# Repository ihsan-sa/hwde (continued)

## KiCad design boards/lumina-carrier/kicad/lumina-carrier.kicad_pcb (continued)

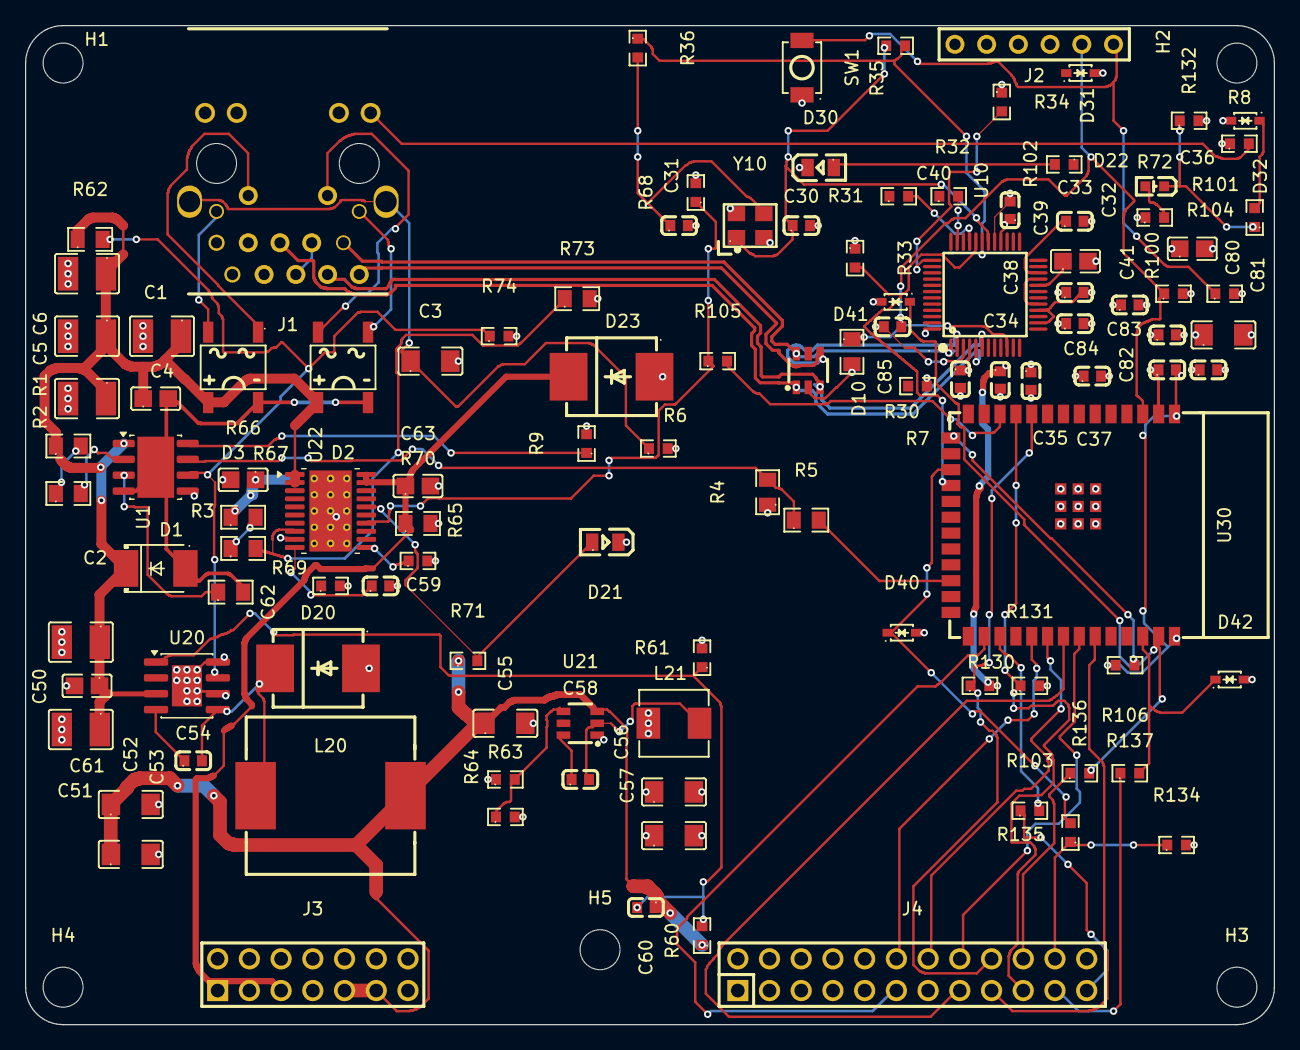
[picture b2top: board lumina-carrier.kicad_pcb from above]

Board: 4 copper layers, 100.0 x 80.0 mm, 116 parts (0 on the bottom side), 85 nets.

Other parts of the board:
H1, H2, H3, H4: MountingHole_3.2mm_M3

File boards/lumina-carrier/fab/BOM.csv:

Comment,Designator,Footprint,LCSC
100nF 100V X7R 0805,"C1,C61,C62,C63",C0805,C28233
10uF 100V X7R 1210,"C2,C4,C5,C6",C1210,C5156756
1nF 2kV X7R 1206,C3,C1206,C9196
27pF 50V NP0 0603,"C30,C31",C0603,C107045
4.7uF 25V X5R 0805,"C32,C36",C0805,C1779
10nF 50V X7R 0603,"C33,C59",C0603,C57112
100nF 50V X7R 0603,"C34,C35,C37,C38,C39,C40,C41,C54,C58",C0603,C14663
2.2uF 100V X7R 1210,"C50,C51",C1210,C153036
22uF 25V X5R 1206,"C52,C53,C55,C56,C57",C1206,C380359
150pF 50V NP0 0603,C60,C0603,C107038
22uF 25V X5R,C80,C1206,C380359
100nF 50V X7R,"C81,C82,C83",C0603,C14663
1uF 50V X5R,"C84,C85",C0603,C15849
SMBJ58A 58V 600W TVS,D1,SMB_L4.3-W3.6-LS5.4-R-RD,C2891331
ABS210 2A 1000V bridge (Alt A),D2,ABF_L5.1-W4.4-P4.00-LS6.2-BL,C2892567
ABS210 2A 1000V bridge (Alt B),D3,ABF_L5.1-W4.4-P4.00-LS6.2-BL,C2892567
TPD4E1U06 4ch 0.55pF ESD array,D10,SOT-23-6_L2.9-W1.6-P0.95-LS2.8-BR,C19829453
SS510C 100V 5A Schottky SMC,"D20,D23",SMC_L7.1-W6.2-LS8.1-R-RD,C19229
Green LED 0805,"D21,D30",LED0805-R-RD,C2297
Red LED 0603,D22,LED-SMD_L1.6-W0.8-R-RD,C2286
PESD3V3L1BA 3.3V ESD clamp SOD-323,"D31,D32,D40,D41,D42",SOD-323_L1.7-W1.3-LS2.6-BI,C2687129
LPJG0926HENL PoE+ RJ45 magjack,J1,RJ45-TH_LPJG0926HENL_C22457393,C22457393
1x6 2.54mm header (recovery),J2,CONN-TH_DS1021-1X6SF11-B,C7430362
DS1021-2x7SF11-B 2x7 male header,J3,HDR-TH_14P-P2.54-V-M-R2-C7-S2.54-1,C7430403
DS1021-2x12SF11-B 2x12 male header,J4,HDR-TH_24P-P2.54-V-M-R2-C12-S2.54,C7430408
68uH 3A 140mohm inductor,L20,IND-SMD_L12.6-W13.5,C526032
4.7uH 4A 46mohm inductor,L21,IND-SMD_L5.4-W5.2,C325964
12.1k 1% 0805,"R1,R2",R0805,C17431
90.9R 1% 0805,R3,R0805,C3000584
10k 1% 0805,"R4,R5",R0805,C17414
1M 1% 0603,"R6,R35",R0603,C22935
330R 1% 0603,"R7,R8,R72",R0603,C23138
0R jumper 0603,"R9,R36",R0603,C21189
12.4k 1% 0805,R30,R0805,C30908
22R 1% 0603,"R31,R32",R0603,C23345
10k 1% 0603,"R33,R34,R64,R69,R71,R106,R132,R134",R0603,C25804
270k 1% 0603,R60,R0603,C22965
30k 1% 0603,"R61,R68",R0603,C22984
100k 1% 0805,"R62,R70",R0805,C149504
33k 1% 0603,R63,R0603,C4216
18k 1% 0603,R65,R0603,C25810
620k 0.1% 0805,R66,R0805,C865592
10k 0.1% 0805,R67,R0805,C110775
12k 0.1% 0805,R73,R0805,C865172
4.7k 1% 0603,"R74,R130,R131",R0603,C23162
10k,"R100,R101",R0603,C25804
330R,R102,R0603,C23138
1k 1% 0603,"R103,R104,R105,R135,R136,R137",R0603,C21190
SMD tactile switch,SW1,SW-SMD_L3.9-W3.0-P4.45,C720477
TPS2378DDAR,U1,SOIC-8-1EP_3.9x4.9mm_P1.27mm_EP2.95x4.9mm_Mask2.71x3.4mm,C337500
W5500,U10,LQFP-48_L7.0-W7.0-P0.50-LS9.0-BL,C32843
SCT2A25STER,U20,SOIC-8-1EP_3.9x4.9mm_P1.27mm_EP2.41x3.3mm,C5124114
TPS563201DDCR,U21,SOT-23-6_L2.9-W1.6-P0.95-LS2.8-BR,C116592
TPS16630PWPR,U22,HTSSOP-20-1EP_4.4x6.5mm_P0.65mm_EP3.4x6.5mm_Mask2.96x2.96mm_ThermalVias,C1849461
ESP32-S3-WROOM-1-N8,U30,WIFIM-SMD_ESP32-S3-WROOM-1-N8,C2913198
25MHz 18pF CL crystal,Y10,OSC-SMD_4P-L3.2-W2.5-BL_SIT8008BI,C70593

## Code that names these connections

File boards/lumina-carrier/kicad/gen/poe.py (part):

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    package takes it all (see "BRIDGE THERMAL" below).
  * U1 exposed pad (9) is VSS, NOT RTN ("The PowerPAD is internally connected
    to VSS", sec 7.3.8/7.3.9). Padding it to RTN destroys the part.
  * U1 pin 8 APD is an INPUT and the datasheet says "If not used, connect APD
    to RTN". Its sink current is 1-3 uA, so a floating APD drifts above the
    1.5 V threshold and turns the pass MOSFET off. Tied through R9 (0 R) so a
    TPS2379 second source - whose pin 8 is GATE and must NOT see RTN - stays
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    MLCC exists on LCSC in any package. ~20-24 uF after DC-bias derating, well
    over the >= 5 uF AC-MPS floor (DS 7.4.7) and far under the ~180 uF port
    ceiling. Do not "fix" this back.
  * D1 SMBJ58A is unidirectional: pin 2 is the CATHODE (to V48_RAW).

BRIDGE THERMAL - why ABS210 and not the obvious MB6S/MB10S
----------------------------------------------------------
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
    sheets.md P4 note 2: V48_RAW / V48_RTN must be GLOBAL bare nets, but KiCad
    ships no power symbol with those names. A local label alone would yield
    /poe/V48_RAW and `netlist_audit --constraints` would raise missing_net at
    ERROR severity (constraints.json.voltages + .power both name them bare).
    So place power:+48V and rewrite its Value, which is what KiCad 6+ derives
    a power symbol's net name from (verified for this build - see
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                     at=(139.70, 152.40),
                     footprint=f"{FP}:SMB_L4.3-W3.6-LS5.4-R-RD",
                     expect={"1": "A", "2": "K"})
    sh.wire_pins("D1", {"1": "V48_RTN", "2": "V48_RAW"})

    # ------------------------------------------------------- LED resistors ---
    # Anode side from +3V3; ~4 mA at Vf 1.8-2.6 V, inside the W5500's IOL.
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    # magjack's LED PINS that swapped colour, not the drive network.
    sh.add_component(SYM_R330, "R7", V_330R, at=(127.00, 44.45),
                     footprint=R0603)
    sh.wire_pins("R7", {"1": "+3V3", "2": "LED_Y_A"})
    sh.add_component(SYM_R330, "R8", V_330R, at=(127.00, 69.85),
                     footprint=R0603)
    sh.wire_pins("R8", {"1": "+3V3", "2": "LED_G_A"})

    # ------------------------------------------------- detection signature ---
    # RDEN from VDD to DEN, split in two with the tap brought out.
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    # why this moved down from 24.8 k now that the bridge diodes are known.
    sh.add_component(SYM_R0805, "R1", V_12K1, at=(177.80, 50.80),
                     footprint=R0805)
    sh.wire_pins("R1", {"1": "V48_RAW", "2": "DEN_TAP"})
    sh.add_component(SYM_R0805, "R2", V_12K1, at=(177.80, 76.20),
                     footprint=R0805)
    sh.wire_pins("R2", {"1": "DEN_TAP", "2": "DEN"})

    # ------------------------------------------------------------ U1 --------
    # Pin 5 RTN is board GND; pin 4 VSS and the pad (9) are V48_RTN.
    # C1 is the IEEE 802.3 detection-window bypass (50-120 nF) across VDD-VSS,
    # so its return is V48_RTN, NOT GND - hence the gnd override.
    # C2/C4/C5/C6 are CBULK, which the datasheet places from VDD (1) to
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    sh.place_ic_with_decoupling(
        "U1", f"{FP}:TPS2378DDAR", "TPS2378DDAR",
        at=(241.30, 114.30),
        pins={"1": "V48_RAW",   # VDD
              "2": "DEN",       # detection signature
              "3": "CLS",       # classification, RCLS to VSS
              "4": "V48_RTN",   # VSS - local ground of the PD front end
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        expect={"1": "VDD", "2": "DEN", "3": "CLS", "4": "VSS", "5": "RTN",
                "6": "CDB", "7": "T2P", "8": "APD", "9": "EP"},
        decoupling=[
            {"cap": "C1", "pin": "1", "rail": "V48_RAW", "gnd": "V48_RTN",
             "value": V_100N, "lib_id": SYM_C100N, "footprint": C0805},
            {"cap": "C2", "pin": "1", "rail": "V48_RAW", "value": V_10U,
             "lib_id": SYM_C10U, "footprint": C1210},
            {"cap": "C4", "pin": "1", "rail": "V48_RAW", "value": V_10U,
             "lib_id": SYM_C10U, "footprint": C1210},
            {"cap": "C5", "pin": "1", "rail": "V48_RAW", "value": V_10U,
             "lib_id": SYM_C10U, "footprint": C1210},
            {"cap": "C6", "pin": "1", "rail": "V48_RAW", "value": V_10U,
             "lib_id": SYM_C10U, "footprint": C1210},
        ],
        caps_at=(139.70, 215.90), caps_dx=25.40)
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    # so the D-01 upgrade is not fitted assuming free thermal headroom.
    r3 = sh.add_component(SYM_R909, "R3", "90.9R 1% 0805",
                          at=(292.10, 165.10), footprint=R0805)
    sh.wire_pins("R3", {"1": "CLS", "2": "V48_RTN"})
    r3.set_property("Note", "D-01 LEVER  af=90R9 / at=63R4")
    r3.set_property("ALT_LCSC", "C334927")
    r3.set_property("ALT_VALUE", "63.4R 1% 0805 = Class 4 / 802.3at "
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    # so a TPS2379 (pin 8 = GATE) can be stuffed on the same footprint.
    sh.add_component(SYM_R0, "R9", "0R jumper 0603", at=(292.10, 114.30),
                     footprint=R0603)
    sh.wire_pins("R9", {"1": "APD", "2": "GND"})

    # ------------------------------------------------------ T2P network ------
    # T2P is open drain to RTN, and RTN is board GND here, so the level shift
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    # pulls it up higher), R5 limits fault current into the ESP32-S3 GPIO.
    sh.add_component(SYM_R10K, "R4", V_10K, at=(317.50, 63.50),
                     footprint=R0805)
    sh.wire_pins("R4", {"1": "+3V3", "2": "T2P_OD"})
    sh.add_component(SYM_R10K, "R5", V_10K, at=(317.50, 88.90),
                     footprint=R0805)
    sh.wire_pins("R5", {"1": "T2P_OD", "2": "T2P"})

    # -------------------------------------------------------- shield hybrid --
    # 1 M bleed || 1 nF / 2 kV: DC-isolates the shell from board ground (which
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    # SERIES with the magjack's internal 1 nF, not in parallel with it, and R6
    # is the only thing defining the shell's DC potential.
    sh.add_component(SYM_R1M, "R6", V_1M, at=(50.80, 177.80), footprint=R0603)
    sh.wire_pins("R6", {"1": "SHIELD", "2": "GND"})
    sh.add_component(SYM_C1N, "C3", V_1N2K, at=(88.90, 177.80),
                     footprint=f"{FP}:C1206")
    sh.wire_pins("C3", {"1": "SHIELD", "2": "GND"})

    # ------------------------------------------------------------ rails ------
    # Every rail on this board is driven by a PASSIVE pin (a connector pin, an
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            ("ETH_RXN", "passive"),
            ("ETH_LED_LINK", "passive"),   # driven by U10 LINKLED, active low
            ("ETH_LED_ACT", "passive"),    # driven by U10 ACTLED, active low
            ("T2P", "output"),             # U1 type-2 flag -> U30 GPIO47
            # CDB is the 8th pin and is NOT in the brief's interface list.
            # sheets.md s1.3 files /poe/CDB as sheet-INTERNAL yet names U20's
            # EN (pwr sheet) as a member, which cannot both be true. Exposing
            # it is the only wiring that matches the architecture's PoE
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
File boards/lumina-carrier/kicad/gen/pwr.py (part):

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    dissipates more than U20 does.
  * U20 EN abs max is **6 V** and it is fed from U1's CDB on the 48 V side,
    so R62/R74 (100 k / 4.7 k) divide V48_RAW down before it ever reaches the
    pin, and double as the programmable input UVLO (see the block comment on
    the divider for the arithmetic and for the CDB-open behaviour).
  * U20 TM (6) is factory-test only - tied to GND, which the datasheet
    explicitly permits ("Connect TM to EN pin, to ground, or leave floating").
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    +48V_SW, anode on GND, physically adjacent to pins 18-20.
  * U22 UVLO/OVP is a THREE-resistor string IN->UVLO->OVP->GND (Figure 8-3).
    R66/R67/R73 were RE-DERIVED this session; see the block comment there.
  * SHDN and OVP are 5.5 V abs-max pins on a 57 V board. Neither may ever be
    exposed to the rail.

DEVIATIONS FROM parts/parts.json (the orchestrator must fold these back)
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        expect={"1": "FB", "2": "NC", "3": "VIN", "4": "BST", "5": "SW",
                "6": "TM", "7": "EN", "8": "GND", "9": "PAD"},
        decoupling=[
            {"cap": "C50", "pin": "3", "rail": "V48_RAW", "value": V_2U2,
             "lib_id": SYM_C2U2, "footprint": C1210},
            {"cap": "C51", "pin": "3", "rail": "V48_RAW", "value": V_2U2,
             "lib_id": SYM_C2U2, "footprint": C1210},
            # NEW REFDES on an existing BOM line (C28233): the datasheet
            # "strongly recommends" a small 0.1 uF right at VIN/GND on top of
            # the bulk. 100 V part - a 50 V 0603 must never sit on this rail.
            {"cap": "C61", "pin": "3", "rail": "V48_RAW",
             "value": V_100N_100V, "lib_id": SYM_C100N_100V,
             "footprint": C0805},
        ],
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    # U1's CDB (open drain, referenced to RTN == board GND on this
    # non-isolated PD) is pulled low only while the PD is in inrush current
    # limiting, and is high-Z otherwise. EN floats HIGH inside the SCT2A25,
    # so the pin cannot simply be tied to CDB: it would sit at the internal
    # pull-up voltage, and if CDB were ever driven from the rail it would
    # exceed the 6 V EN ABS MAX.
    #
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    # recommended (5 mA abs max) sink and far below its 0.5 V max VOL.
    sh.add_component(SYM_R100K, "R62", V_100K, at=(38.10, 38.10),
                     footprint=R0805)
    sh.wire_pins("R62", {"1": "V48_RAW", "2": "CDB"})
    sh.add_component(SYM_R4K7, "R74", V_4K7, at=(38.10, 63.50),
                     footprint=R0603)
    sh.wire_pins("R74", {"1": "CDB", "2": "GND"})

    # ------------------------------------------------ U20 power stage -------
    # BST-SW 0.1 uF, X5R or better, >= 10 V: mandatory ("must be connected").
    sh.add_component(SYM_C100N, "C54", V_100N, at=(165.10, 25.40),
                     footprint=C0603)
    sh.wire_pins("C54", {"1": "BST", "2": "SW"})
    sh.add_component(f"{FP}:FXL1360-680-M", "L20", "68uH 3A 140mohm inductor",
                     at=(165.10, 50.80),
                     footprint=f"{FP}:IND-SMD_L12.6-W13.5")
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    # 0.1 uF VBST-SW: "must be connected ... for proper operation".
    sh.add_component(SYM_C100N, "C58", V_100N, at=(254.00, 50.80),
                     footprint=C0603)
    sh.wire_pins("C58", {"1": "BST33", "2": "SW33"})
    # L21 is the 4.7 uH end of the datasheet's 2.2 uH typ / 4.7 uH max window
    # for 3.3 V - legal, and deliberate: 46 mohm and 4.5 A saturation against a
    # 1.0 A design rail with 1.21 A ms-scale peaks. Higher L = lower ripple and
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    sh.place_ic_with_decoupling(
        "U22", f"{FP}:TPS16630PWPR", "TPS16630PWPR",
        at=(139.70, 203.20),
        pins={"1": "V48_RAW", "2": "V48_RAW", "3": "V48_RAW",
              "4": "NC", "5": "NC",
              "6": "V48_RAW",     # P_IN: "Always connect P_IN to IN directly"
              "7": "UVLO",
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            # external capacitance on IN/P_IN and on OUT. The >= 1 uF the
            # surge note asks for is already present upstream as poe's
            # 4 x 10 uF CBULK on the same V48_RAW node.
            {"cap": "C62", "pin": "1", "rail": "V48_RAW",
             "value": V_100N_100V, "lib_id": SYM_C100N_100V,
             "footprint": C0805},
            {"cap": "C63", "pin": "18", "rail": "+48V_SW",
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    # (R66+R67)/R73 is only 52.33..52.68; 12 k puts it at 52.500, mid-window.
    #
    # UVLO must never float (sec 8.3.2) - it is fed by this string, always.
    # OVP is a 4 V rec / 5.5 V abs-max pin: it only ever sees ~1.2 V here, and
    # R67/R73 are 0805 so that an open R66 cannot expose them to the rail.
    sh.add_component(SYM_R0805, "R66", V_620K, at=(44.45, 165.10),
                     footprint=R0805)
    sh.wire_pins("R66", {"1": "V48_RAW", "2": "UVLO"})
    sh.add_component(SYM_R0805, "R67", V_10K_0805, at=(44.45, 177.80),
                     footprint=R0805)
    sh.wire_pins("R67", {"1": "UVLO", "2": "OVP"})
    sh.add_component(SYM_R0805, "R73", V_12K, at=(44.45, 190.50),
                     footprint=R0805)
    sh.wire_pins("R73", {"1": "OVP", "2": "GND"})

    # ------------------------------------------------------------- ILIM ----
    # R(ILIM) = 18 / I(OL) with R in kohm and I in A (Eq 6/10), so 18 k = a
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    # Recommended range 3-30 kohm, and UL 2367 needs >= 3 kohm.
    sh.add_component(SYM_R0603, "R65", V_18K, at=(44.45, 215.90),
                     footprint=R0603)
    sh.wire_pins("R65", {"1": "ILIM", "2": "GND"})

    # ------------------------------------------------------------- dVdT ----
    # 10 nF = the datasheet MINIMUM when the pin is used (the timing table is
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    # daughter owns its inrush ramp, exactly as blocks.md requires.
    sh.add_component(SYM_C10N, "C59", V_10N, at=(44.45, 228.60),
                     footprint=C0603)
    sh.wire_pins("C59", {"1": "DVDT", "2": "GND"})

    # ------------------------------------------------------------- IMON ----
    # V(IMON) = I(OUT) x 27.9 uA/A x R68 -> 0.837 V at the 1.0 A limit and
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    # NO CAPACITOR on this node (sec 8.3.6) - a bypass delays the reading.
    sh.add_component(SYM_R30K, "R68", V_30K, at=(44.45, 241.30),
                     footprint=R0603)
    sh.wire_pins("R68", {"1": "IMON", "2": "GND"})

    # ================= THE CAR-REQ-08 FAIL-SAFE - DO NOT REMOVE =============
    # SHDN is ACTIVE LOW with an INTERNAL PULL-UP: open-circuit 2.48 V min /
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    # Hardware-driven, no GPIO.
    sh.add_component(SYM_R10K, "R71", V_10K, at=(215.90, 190.50),
                     footprint=R0603)
    sh.wire_pins("R71", {"1": "+12V", "2": "PGOOD"})
    sh.add_component(f"{FP}:0805G", "D21", "Green LED 0805",
                     at=(215.90, 203.20), footprint=f"{FP}:LED0805-R-RD",
                     expect={"1": "A", "2": "K"})
    sh.wire_pins("D21", {"1": "PGOOD", "2": "GND"})

    # D22, FAULT (red). FLT is open drain ACTIVE LOW, so the natural low-side
    # topology has the right polarity: +3V3 -> R72 -> D22 -> FLT.
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    # would leave /FAULT floating around 1.7 V. Hardware-driven, no GPIO.
    sh.add_component(SYM_R330, "R72", V_330R, at=(215.90, 228.60),
                     footprint=R0603)
    sh.wire_pins("R72", {"1": "+3V3", "2": "FLT_LED"})
    sh.add_component(f"{FP}:KT-0603R", "D22", "Red LED 0603",
                     at=(215.90, 241.30),
                     footprint=f"{FP}:LED-SMD_L1.6-W0.8-R-RD",
                     expect={"1": "A", "2": "K"})
    sh.wire_pins("D22", {"1": "FLT_LED", "2": "FAULT"})

    # =====================================================================
    # rails
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    # Shape follows poe.py's rule - `passive` for nets another sheet drives,
    # `output` only where THIS sheet is the driver.
    #
    # CDB is the 4th pin and is NOT in this sheet's briefed interface list.
    # sheets.md s1.3 files /poe/CDB as poe-INTERNAL while naming U20's EN (on
    # THIS sheet) as a member, which cannot both be true; poe.py has already
    # resolved it the same way by exposing CDB as an output. The root MUST
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
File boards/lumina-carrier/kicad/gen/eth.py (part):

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DEVIATIONS from architecture/sheets.md, and why
-----------------------------------------------
1. SPI series resistors split their nets. sheets.md s1.2 lists R31 as a
   MEMBER of `/ETH_SCLK` alongside both U10 SCLK and U30 GPIO12, but s2.2
   specifies R31/R32 as "22-33 ohm SERIES, at the driver pin" - a series
   element cannot leave one net. Resolved in favour of s2.2 (the more
   specific component-level statement): the hierarchical pin sits on the
   MCU-facing terminal, so `/ETH_SCLK` and `/ETH_MOSI` still cross the root
   exactly as constraints.json declares (`/ETH_SCLK` is a `high_speed`
   entry - if it stopped crossing, it would be renamed and
   check_return_path would raise CheckError -> exit 2). The PHY-side stubs
   become `/eth/SCLK_PHY` and `/eth/MOSI_PHY`, which no constraint names.
   Both resistors are intended for the DRIVER end: U30 drives SCLK and
   MOSI, so P6 must place R31/R32 next to U30, not next to U10
   (sheets.md s2.2: "placed at U30's end").
2. The crystal leg needs a third internal net. sheets.md s1.3 names only
   `/eth/XI` and `/eth/XO`, but the datasheet's 0 ohm series resistor in the
   XO leg splits XO into `/eth/XO` (U10 pin 31 side) and `/eth/XO_XTAL`
   (crystal + C31 side). Neither name is referenced by constraints.json.
3. R35 (1 M feedback) and R36 (0 R series) are NOT in parts/parts.json's
   refs lists. They re-use existing BOM lines - C22935 (1 M 1 % 0603, today
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            # should be short to stabilize the internal signals" as an
            # explicit 5 mm proximity warn threshold (the 4.7 uF value would
            # otherwise class as "bulk" and not complain until 20 mm).
            {"cap": "C32", "pin": "20", "rail": "TOCAP",
             "rail_net": "/eth/TOCAP", "value": V_4U7, "lib_id": S_C_4U7,
             "footprint": F_C0805, "max_dist_mm": 5.0},
            {"cap": "C33", "pin": "22", "rail": "1V2O",
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    # the transmit amplitude, so the 1 % tolerance is functional, not habit.
    sh.add_component(S_R_12K4, "R30", "12.4k 1% 0805", at=(114.3, 215.9),
                     footprint=F_R0805)
    sh.wire_pins("R30", {"1": "EXRES", "2": "GND"})

    # ================================================ 25 MHz crystal group
    # DS Figure 3: crystal across XI/XO, 1 M feedback across XI-XO, 0 R in
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    sh.wire_pins("R35", {"1": "XI", "2": "XO"})
    sh.add_component(S_R_0R, "R36", "0R jumper 0603", at=(228.6, 177.8),
                     footprint=F_R0603)
    sh.wire_pins("R36", {"1": "XO", "2": "XO_XTAL"})
    # Y10: symbol Reference default is "X" - the refdes below is the one
    # parts/parts.json assigns, and constraints.json's eth_xtal group and
    # Y10<->J1 25 mm separation both key on it.
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                     at=(271.78, 177.8), footprint=F_Y10,
                     expect={"1": "OSC1", "2": "GND", "3": "OSC2",
                             "4": "GND"})
    sh.wire_pins("Y10", {"1": "XI", "3": "XO_XTAL", "2": "GND", "4": "GND"})
    # 27 pF NP0 = 2 x (CL 18 pF - ~4.5 pF stray). Expect to trim on proto 1.
    sh.add_component(S_C_27P, "C30", V_27P, at=(228.6, 190.5),
                     footprint=F_C0603)
    sh.wire_pins("C30", {"1": "XI", "2": "GND"})
    sh.add_component(S_C_27P, "C31", V_27P, at=(228.6, 203.2),
                     footprint=F_C0603)
    sh.wire_pins("C31", {"1": "XO_XTAL", "2": "GND"})

    # ======================================================= MDI ESD array
    # D10 TPD4E1U06, PHY side of the magnetics, at the J1 end of the pairs.
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    # The easyeda2kicad pull had pins 1 and 4 LABELLED backwards ("D1+" on
    # pin 1, "D2-" on pin 4) against the datasheet's 1 = D2-, 4 = D1+. The
    # netlist was always correct (wiring is by pin number), but the sheet
    # and the PDF showed ETH_TXP arriving on a pin captioned "D2-", which is
    # a trap for the layout and DFM readers. The symbol was repaired in
    # lib/aiee.kicad_sym (lib/EDITS.md edit 6); `expect` now asserts ALL SIX
    # names, so the mismatch cannot silently come back on a lib re-pull.
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    # hierarchical pin sits on the MCU-facing terminal.
    sh.add_component(S_R_22R, "R31", "22R 1% 0603", at=(241.3, 106.68),
                     footprint=F_R0603)
    sh.wire_pins("R31", {"1": "ETH_SCLK", "2": "SCLK_PHY"})
    sh.add_component(S_R_22R, "R32", "22R 1% 0603", at=(241.3, 119.38),
                     footprint=F_R0603)
    sh.wire_pins("R32", {"1": "ETH_MOSI", "2": "MOSI_PHY"})
    # R33 is MANDATORY, not hygiene: ESP32-S3 GPIO10 glitches low for ~60 us
    # at power-up and low = W5500 selected, so without it the PHY sees a
    # spurious frame before firmware runs. The W5500's own 50/77/112 k
    # internal pull-up is too weak to be relied on against that.
    sh.add_component(S_R_10K, "R33", "10k 1% 0603", at=(241.3, 132.08),
                     footprint=F_R0603)
    sh.wire_pins("R33", {"1": "+3V3", "2": "ETH_CSn"})
    # R34: belt and braces on RSTn (the W5500 has an internal pull-up too).
    sh.add_component(S_R_10K, "R34", "10k 1% 0603", at=(241.3, 144.78),
                     footprint=F_R0603)
    sh.wire_pins("R34", {"1": "+3V3", "2": "ETH_RSTn"})

    # ================================================== hierarchical exports
    # Free-cluster variant per sheets.md s3.3: a local label at one end and
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
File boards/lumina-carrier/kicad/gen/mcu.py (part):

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    "30": "FAULT_M",    # IO37 - input, open-drain wire-OR (pull-up on J4/pwr)
                        #        Via R104 1k + D32 clamp.
    "31": "PWM7",       # IO38 - LEDC ch7, timer 1
    "32": "DSPI_SCK",   # IO39 - SPI3 via the GPIO matrix; forfeits JTAG MTCK
    "33": "DSPI_MOSI",  # IO40 - forfeits MTDO
    "34": "DSPI_MISO",  # IO41 - forfeits MTDI
    "35": "DSPI_CSn",   # IO42 - forfeits MTMS
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# geometry contract as schlib.wire_pin - stub from the real pin position,
# label ON the wire endpoint.
U30_PINS_BOTTOM = {
    "15": "IO3_STRAP",  # IO3  - strapping, NO internal pull -> R106 10k down
    "16": "NC",         # IO46 - strapping, weak pull-down - see note above
    "17": "ID_ADC",     # IO9  - ADC1_CH8, daughter ID divider
    "18": "ETH_CSn",    # IO10 - FSPICS0 (IO_MUX); 10k pull-up on the eth sheet
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    "20": "ETH_SCLK",   # IO12 - FSPICLK
    "21": "ETH_MISO",   # IO13 - FSPIQ
    "22": "ETH_INTn",   # IO14 - FSPIWP, unused in 4-wire SPI
    "23": "ETH_RSTn",   # IO21 - plain GPIO, no ADC, no power-up glitch
    "24": "T2P",        # IO47 - Type-2 flag via U1's level shift on `poe`
    "25": "STATUS",     # IO48 - firmware heartbeat LED D30
    "26": "NC",         # IO45 - BRICK RISK, must not be pulled high
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    # pin 1 = A on the right).
    sh.add_component("aiee:0603WAF3300T5E", "R102", "330R", at=(215.90, 228.60),
                     footprint=f"{FP}:R0603")
    sh.wire_pins("R102", {"1": "STATUS", "2": "STATUS_A"})
    sh.add_component("aiee:0805G", "D30", "Green LED 0805", at=(254.00, 228.60),
                     rotation=180, footprint=f"{FP}:LED0805-R-RD",
                     expect={"1": "A", "2": "K"})
    sh.wire_pins("D30", {"1": "STATUS_A", "2": "GND"})

    # ---- connector-facing signal protection, at the MCU end ---------------
    # /ENABLE and /FAULT run to J4 pins 23/24 on a user-mateable 2.54 mm
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    # PESD3V3L1BA (R135/D40, R136/D41, R137/D42 on `expansion`); these two
    # digital ones had nothing. Same chain, mirrored to this end:
    #
    #     J4 pin ---- /ENABLE ---- R103 1k ---- /mcu/ENABLE_M ---- U30 IO36
    #                   |                              |
    #              U22 SHDN + R69                     D31 -> GND
    #
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        sh.wire_pins(d_ref, {"1": f"{net}_M", "2": "GND"})

    # ---- /IMON series resistor -------------------------------------------
    # V(IMON) = I_OUT x 27.9 uA/A x R68(30k) = 0.837 V/A. The ESP32-S3 GPIO
    # abs max is VDD+0.3 = 3.6 V, which IMON reaches at I_OUT = 4.30 A -
    # above U22's 1.0 A overload limit and its 2.0 A fast-trip, but BELOW the
    # 45 A / 1 us hard short-circuit threshold, so during a hard short the
    # pin can be driven over 3.6 V for ~1 us. IMON is a current source
    # limited to I_OUT x 27.9 uA/A <= 1.26 mA at 45 A, so the GPIO's clamp
    # diode would survive it, but it is formally out of spec. R105 1 k drops
    # the source impedance into the clamp to a defined value and costs
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    # calibrates out; the ADC input leakage is nA, so there is no offset).
    sh.add_component(S_R_1K, "R105", V_1K, at=(215.90, 139.70),
                     footprint=f"{FP}:R0603")
    sh.wire_pins("R105", {"1": "IMON", "2": "IMON_M"})

    # ---- IO3 strapping pull-down -----------------------------------------
    # parts/C2913198.json, IO3: "STRAPPING PIN (JTAG signal source select)
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    # brick boot on this 3.3 V-flash -N8 SKU.
    sh.add_component(S_R_10K, "R106", V_10K, at=(215.90, 165.10),
                     footprint=f"{FP}:R0603")
    sh.wire_pins("R106", {"1": "IO3_STRAP", "2": "GND"})

    # ---- cross-sheet pins -------------------------------------------------
    # Free-cluster variant (sheets.md s3 note 3): a local label of the net
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
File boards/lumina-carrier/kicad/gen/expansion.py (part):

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    # ================================= I2C pull-ups + FAULT pull-up (ICD s3.3)
    sh.add_component(S_R_4K7, "R130", V_4K7, at=(190.5, 55.88),
                     footprint=F_R0603)
    sh.wire_pins("R130", {"1": "I2C_SCL", "2": "+3V3"})
    sh.add_component(S_R_4K7, "R131", V_4K7, at=(190.5, 76.2),
                     footprint=F_R0603)
    sh.wire_pins("R131", {"1": "I2C_SDA", "2": "+3V3"})
    # FAULT: open drain from the daughter, wire-OR'd with U22's FLT on the
    # `pwr` sheet. This is the ONLY pull-up on the net board-wide.
    sh.add_component(S_R_10K, "R132", V_10K, at=(190.5, 96.52),
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    # error. Unmated, ID_ADC_CONN is pulled to +3V3 = "no daughter".
    sh.add_component(S_R_10K, "R134", V_10K, at=(190.5, 116.84),
                     footprint=F_R0603)
    sh.wire_pins("R134", {"1": "ID_ADC_CONN", "2": "+3V3"})

    # ============= series protection + 3V3 clamps on the three analogue lines
    # Chain per line:  J4 pin -> <NET>_CONN -> 1k -> <NET> -> clamp -> GND
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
